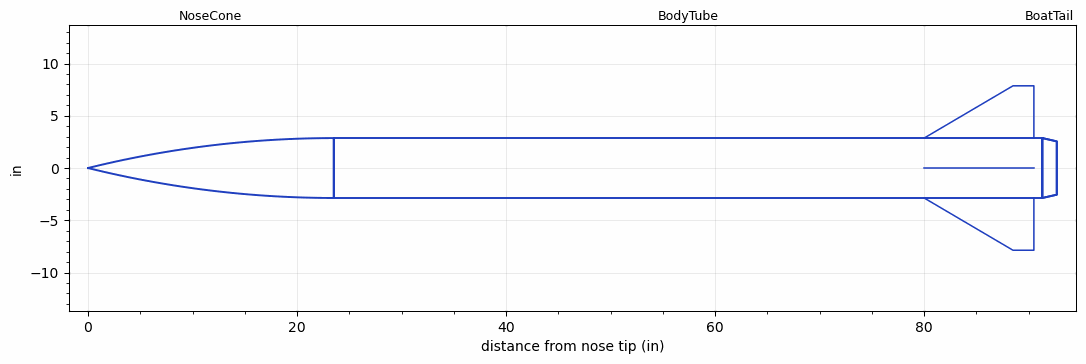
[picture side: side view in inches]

<RASAeroDocument>
 <FileVersion>2</FileVersion>
 <RocketDesign>
  <NoseCone>
   <Length>23.5</Length>
   <Diameter>5.73</Diameter>
   <Shape>Tangent Ogive</Shape>
   <Location>0</Location>
  </NoseCone>
  <BodyTube>
   <Length>67.809</Length>
   <Diameter>5.73</Diameter>
   <Location>23.5</Location>
   <BoattailLength>1.375</BoattailLength>
   <BoattailRearDiameter>5.1</BoattailRearDiameter>
   <Fin>
    <Count>4</Count>
    <Chord>10.5</Chord>
    <Span>5</Span>
    <SweepDistance>8.5</SweepDistance>
    <TipChord>2</TipChord>
    <Thickness>0.5397</Thickness>
    <Location>11.315</Location>
    <AirfoilSection>Double Wedge</AirfoilSection>
    <FX1>3.125</FX1>
   </Fin>
  </BodyTube>
  <BoatTail>
   <Length>1.375</Length>
   <Diameter>5.73</Diameter>
   <RearDiameter>5.1</RearDiameter>
   <Location>91.309</Location>
  </BoatTail>
  <Surface>Camouflage Paint</Surface>
  <ModifiedBarrowman>False</ModifiedBarrowman>
  <Turbulence>False</Turbulence>
  <UseBooster1>False</UseBooster1>
  <UseBooster2>False</UseBooster2>
 </RocketDesign>
 <LaunchSite>
  <Altitude>1214</Altitude>
  <Pressure>28.64</Pressure>
  <RodAngle>6</RodAngle>
  <RodLength>203.94</RodLength>
  <Temperature>68</Temperature>
  <WindSpeed>15.53</WindSpeed>
 </LaunchSite>
 <Recovery>
  <Altitude1>656.168</Altitude1>
  <Altitude2>1500</Altitude2>
  <DeviceType1>Parachute</DeviceType1>
  <DeviceType2>Parachute</DeviceType2>
  <Event1>True</Event1>
  <Event2>True</Event2>
  <Size1>31.8897</Size1>
  <Size2>158.2674</Size2>
  <EventType1>Apogee</EventType1>
  <EventType2>Altitude</EventType2>
  <CD1>1.5</CD1>
  <CD2>0</CD2>
 </Recovery>
 <SimulationList>
  <Simulation>
   <SustainerEngine>N2540-GR-P  (CTI)</SustainerEngine>
   <SustainerLaunchWt>58.36</SustainerLaunchWt>
   <SustainerNozzleDiameter>2.7</SustainerNozzleDiameter>
   <SustainerCG>58.93</SustainerCG>
   <SustainerIgnitionDelay>0</SustainerIgnitionDelay>
   <Booster1SeparationDelay>0</Booster1SeparationDelay>
   <Booster1IgnitionDelay>0</Booster1IgnitionDelay>
   <IncludeBooster1>False</IncludeBooster1>
   <Booster2Delay>0</Booster2Delay>
   <IncludeBooster2>False</IncludeBooster2>
   <TimetoApogee>39.40939</TimetoApogee>
   <MaxAltitude>29305.83</MaxAltitude>
   <MaxVelocity>2074.216</MaxVelocity>
  </Simulation>
  <Simulation>
   <SustainerLaunchWt>65.9603</SustainerLaunchWt>
   <SustainerCG>65.3991</SustainerCG>
   <SustainerIgnitionDelay>0</SustainerIgnitionDelay>
   <Booster1SeparationDelay>0</Booster1SeparationDelay>
   <Booster1IgnitionDelay>0</Booster1IgnitionDelay>
   <IncludeBooster1>False</IncludeBooster1>
   <Booster2Delay>0</Booster2Delay>
   <IncludeBooster2>False</IncludeBooster2>
  </Simulation>
  <Simulation>
   <SustainerLaunchWt>64.7224</SustainerLaunchWt>
   <SustainerCG>65.2686</SustainerCG>
   <SustainerIgnitionDelay>0</SustainerIgnitionDelay>
   <Booster1SeparationDelay>0</Booster1SeparationDelay>
   <Booster1IgnitionDelay>0</Booster1IgnitionDelay>
   <IncludeBooster1>False</IncludeBooster1>
   <Booster2Delay>0</Booster2Delay>
   <IncludeBooster2>False</IncludeBooster2>
  </Simulation>
  <Simulation>
   <SustainerLaunchWt>55.8785</SustainerLaunchWt>
   <SustainerCG>66.1409</SustainerCG>
   <SustainerIgnitionDelay>0</SustainerIgnitionDelay>
   <Booster1SeparationDelay>0</Booster1SeparationDelay>
   <Booster1IgnitionDelay>0</Booster1IgnitionDelay>
   <IncludeBooster1>False</IncludeBooster1>
   <Booster2Delay>0</Booster2Delay>
   <IncludeBooster2>False</IncludeBooster2>
  </Simulation>
 </SimulationList>
</RASAeroDocument>
